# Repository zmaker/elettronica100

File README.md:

# elettronica100
Raccolta di slide e progetti del video corso Elettronica 100

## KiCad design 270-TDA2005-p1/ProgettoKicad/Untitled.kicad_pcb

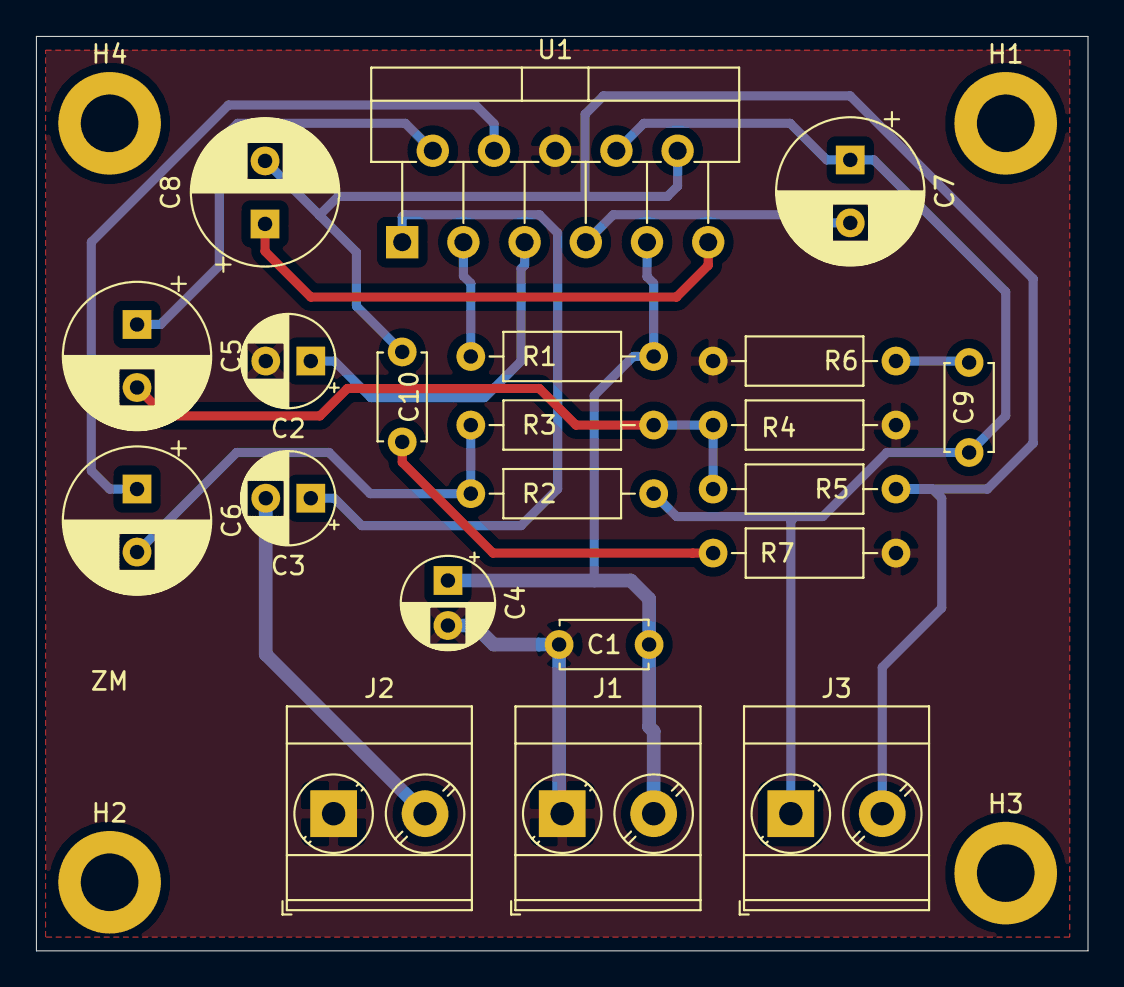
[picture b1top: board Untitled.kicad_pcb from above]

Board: 2 copper layers, 58.4 x 50.8 mm, 25 parts (0 on the bottom side), 16 nets.

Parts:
C1, C9, C10: 100n; C_Disc_D4.7mm_W2.5mm_P5.00mm
C2, C3: 2.2u; CP_Radial_D5.0mm_P2.50mm
C4: 10u; CP_Radial_D5.0mm_P2.50mm
C5, C6: 220u; CP_Radial_D8.0mm_P3.50mm
C7, C8: 100u; CP_Radial_D8.0mm_P3.50mm
H1, H2, H3, H4: MountingHole; MountingHole_3.2mm_M3_ISO7380_Pad
J1, J2, J3: Screw_Terminal_01x02; TerminalBlock_Phoenix_MKDS-3-2-5.08_1x02_P5.08mm_Horizontal
R1: 120k; R_Axial_DIN0207_L6.3mm_D2.5mm_P10.16mm_Horizontal
R2: 2K; R_Axial_DIN0207_L6.3mm_D2.5mm_P10.16mm_Horizontal
R3, R4: 12R; R_Axial_DIN0207_L6.3mm_D2.5mm_P10.16mm_Horizontal
R5: 1k2; R_Axial_DIN0207_L6.3mm_D2.5mm_P10.16mm_Horizontal
R6, R7: 1R; R_Axial_DIN0207_L6.3mm_D2.5mm_P10.16mm_Horizontal
U1: TDA2005; TO-220-11_P3.4x5.08mm_StaggerOdd_Lead4.85mm_Vertical

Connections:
+12V: C1.1, C4.1, J1.2, R1.1, U1.9
A: C5.2, R3.2, R4.1, R5.2
GND: C1.2, C2.2, C4.2, J1.1, J2.1, R4.2, R6.2, R7.2, U1.6
unnamed: C2.1, U1.5
unnamed: C3.1, U1.1
unnamed: C3.2, J2.2
unnamed: C5.1, U1.2
unnamed: C6.1, U1.4
unnamed: C6.2, R2.2, R3.1
unnamed: C7.1, C9.1, J3.1, R2.1, U1.8
unnamed: C7.2, U1.7
unnamed: C8.1, U1.11
unnamed: C9.2, R6.1
unnamed: C8.2, C10.1, J3.2, R5.1, U1.10
unnamed: C10.2, R7.1
unnamed: R1.2, U1.3

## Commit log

2018-11-23 first schematic release
2018-11-26 fino alla 004
2018-11-27 fino alla 004 fix
2018-12-08 fino alla 7
2019-01-06 fino al 15
2019-01-22 22 gennaio
2019-01-28 condensatori
2019-02-15 induttori
2019-02-24 trasf
2019-02-28 semicond
2019-03-10 oscill e diodi
2019-03-18 diodi
2019-04-01 saldare
2019-04-09 9 aprile
2019-04-19 fine aprile
2019-05-04 fix sat bjt
2019-05-12 bjt 2
2019-05-18 polarizzazione bjt
2019-06-03 bjt e-com
2019-06-14 efollow
2019-06-30 fine giugno
2019-07-29 fino a 92
2019-08-30 video settembre
2019-09-14 meta settembre
2019-09-25 sett-ott
2019-10-04 ottobre
2019-11-04 triac
2019-11-25 nov meta
2019-12-02 nov 2nd
2019-12-13 fasori elettr
2019-12-21 natale
2019-12-30 opamp-spice
2020-01-09 opamp
2020-02-10 nodered
2020-02-18 meta febb
2020-02-26 schmitt
2020-03-14 06 mar
2020-03-15 fix rc
2020-03-19 fine marzo
2020-03-23 con cover
2020-03-31 powershield
2020-04-04 RCfix
2020-04-06 peristaltica
2020-04-22 nnet
2020-05-09 maggio 2020 1
2020-07-02 oscilloscpio
2020-07-20 oscilloscopio
2020-08-03 agosto
2020-08-11 fino a meta settembre
2020-09-25 fix numeri progetti
2020-10-18 meta ottobre
2020-11-12 novembre
2020-12-14 dec 2020
2021-01-14 jan 2021 2
2021-01-23 jan 2021 3
2021-01-24 ??
    modifica su file chitarra
2021-01-31 febb 1 -
    febb 1 - chip vari
2021-02-04 fix led girato
    fix led girato
2021-02-17 febb 2 - registri
    registri sipo piso
2021-03-03 marzo 2021
    marzo 2021
2021-03-12 13mar21
    13mar21
2021-03-16 16mar
    16mar
2021-03-25 marzo
    marzo
2021-04-03 .
    .
2023-12-29 new cover
    noise gen
2025-01-13 wincupl
2025-02-08 fli flop
2025-11-03 triac
    .
2025-11-03 fix num
2025-11-08 fix triac
